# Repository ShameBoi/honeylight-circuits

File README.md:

# Circuit files for Honeylight

KiCad project files for the Honeylight LED board and the Honeylight power/processor board.

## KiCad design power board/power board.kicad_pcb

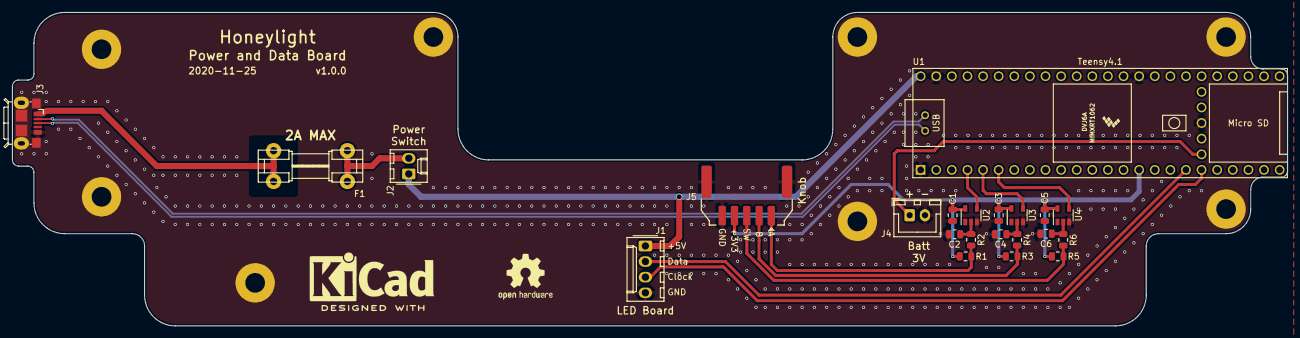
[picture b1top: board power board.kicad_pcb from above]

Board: 2 copper layers, 207.5 x 51.0 mm, 30 parts (0 on the bottom side), 19 nets.

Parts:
C1, C3, C5: 100nF; C_0805_2012Metric
C2, C4, C6: 10nF; C_0805_2012Metric
F1: 2A; Fuseholder5x15_horiz_open_lateral_Type-II
H1: Hole A; MountingHole_3.2mm_M3_Pad
H2: Hole B; MountingHole_3.2mm_M3_Pad
H3: Hole C; MountingHole_3.2mm_M3_Pad
H4: Hole D; MountingHole_3.2mm_M3_Pad
H5: Hole E; MountingHole_3.2mm_M3_Pad
H6: Hole F; MountingHole_3.2mm_M3_Pad
H7: Hole G; MountingHole_3.2mm_M3_Pad
H8: Hole H; MountingHole_3.2mm_M3_Pad
J1: LED Board; Molex_KK-254_AE-6410-04A_1x04_P2.54mm_Vertical
J2: Power Switch; Molex_KK-254_AE-6410-02A_1x02_P2.54mm_Vertical
J3: USB In; USB-Micro-B-FCI-10118193-0001LF
J4: Batt; JST_XH_B2B-XH-A_1x02_P2.50mm_Vertical
J5: Knob; Molex_DuraClik_502352-05XX_1x05-1MP-P2.00mm_SMD_Horizontal
R1, R3, R5: 10K; R_0805_2012Metric
R2, R4, R6: 100; R_0805_2012Metric
U1: Teensy4.1; Teensy41
U2, U3, U4: 74AHC1G14; SOT-23-5

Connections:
+3V3: C1.1, C3.1, C5.1, J5.4, R1.1, R3.1, R5.1, U1.15, U2.5, U3.5, U4.5
+5V: J1.1, J2.1, U1.48
/Clock: J1.3, U1.19
/D+: J3.3, U1.67
/D-: J3.2, U1.66
/Data: J1.2, U1.18
/Debounce Encoder A/Input-Filter: C2.1, R2.1, U2.2
/Debounce Encoder B/Input-Filter: C4.1, R4.1, U3.2
/Debounce Switch/Input-Filter: C6.1, R6.1, U4.2
/Debounced-Encoder-A: U1.4, U2.4
/Debounced-Encoder-B: U1.5, U3.4
/Debounced-Switch: U1.6, U4.4
/Knob-Encoder-A: J5.1, R1.2, R2.2
/Knob-Encoder-B: J5.2, R3.2, R4.2
/Knob-SW: J5.3, R5.2, R6.2
/VBUS-Raw: F1.1, J3.1
/VBatt: J4.1, U1.50
GND: C1.2, C2.2, C3.2, C4.2, C5.2, C6.2, H1.1, H2.1, H3.1, H4.1, H5.1, H6.1, H7.1, H8.1, J1.4, J3.5, J3.6, J4.2, J5.5, J5.MP, U1.1, U1.34, U1.47, U1.52, U2.3, U3.3, U4.3
unnamed: F1.2, J2.2

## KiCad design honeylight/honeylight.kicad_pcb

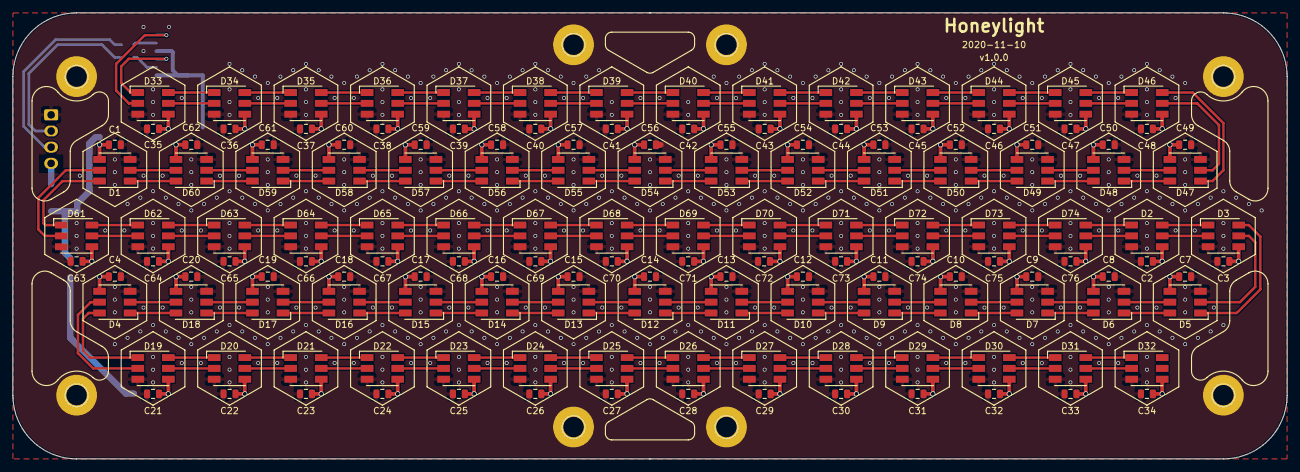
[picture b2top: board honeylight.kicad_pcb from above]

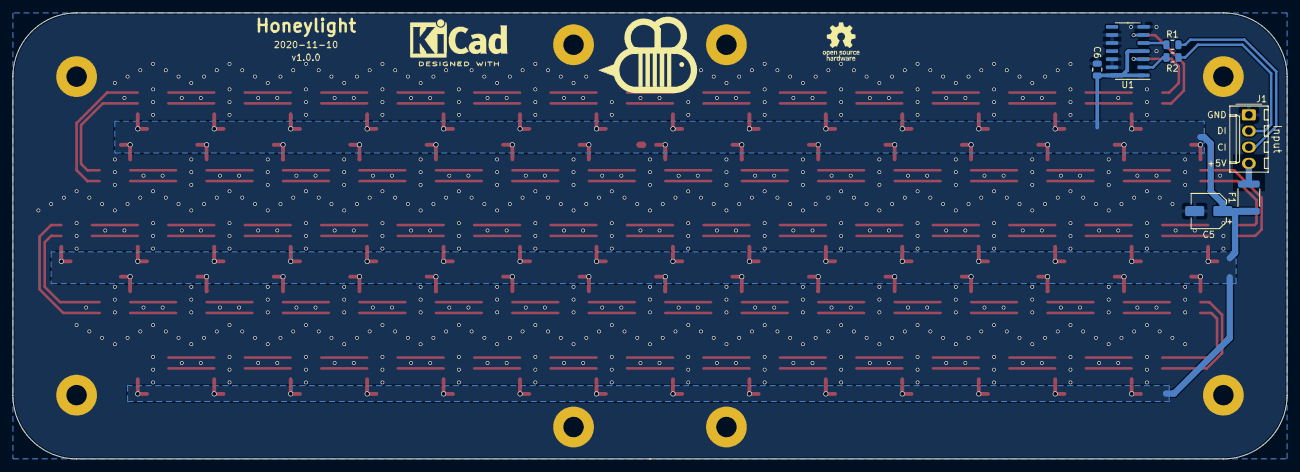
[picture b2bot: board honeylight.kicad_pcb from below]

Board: 2 copper layers, 200.0 x 70.0 mm, 163 parts (7 on the bottom side), 155 nets.

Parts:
C1, C2, C3, C4, C6, C7, C8, C9, C10, C11, C12, C13, C14, C15, C16, C17, C18, C19, C20, C21, C22, C23, C24, C25, C26, C27, C28, C29, C30, C31, C32, C33, C34, C35, C36, C37, C38, C39, C40, C41, C42, C43, C44, C45, C46, C47, C48, C49, C50, C51, C52, C53, C54, C55, C56, C57, C58, C59, C60, C61, C62, C63, C64, C65, C66, C67, C68, C69, C70, C71, C72, C73, C74, C75, C76: 100nF; C_0805_2012Metric
C5: 120uF; CP_Elec_5x5.8
D1, D2, D3, D4, D5, D6, D7, D8, D9, D10, D11, D12, D13, D14, D15, D16, D17, D18, D19, D20, D21, D22, D23, D24, D25, D26, D27, D28, D29, D30, D31, D32, D33, D34, D35, D36, D37, D38, D39, D40, D41, D42, D43, D44, D45, D46, D47, D48, D49, D50, D51, D52, D53, D54, D55, D56, D57, D58, D59, D60, D61, D62, D63, D64, D65, D66, D67, D68, D69, D70, D71, D72, D73, D74: APA102C; LED_RGB_5050-6
F1: 1.25A; Fuse_1812_4532Metric
H1: Hole A; MountingHole_3.2mm_M3_Pad
H2: Hole B; MountingHole_3.2mm_M3_Pad
H3: Hole C; MountingHole_3.2mm_M3_Pad
H4: Hole D; MountingHole_3.2mm_M3_Pad
H5: Hole E; MountingHole_3.2mm_M3_Pad
H6: Hole F; MountingHole_3.2mm_M3_Pad
H7: Hole G; MountingHole_3.2mm_M3_Pad
H8: Hole H; MountingHole_3.2mm_M3_Pad
J1: Input; Molex_KK-254_AE-6410-04A_1x04_P2.54mm_Vertical
R1, R2: 22; R_0805_2012Metric
U1: 74AHCT126; SOIC-14_3.9x8.7mm_P1.27mm

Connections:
+5V: C1.1, C2.1, C3.1, C4.1, C5.1, C6.2, C7.1, C8.1, C9.1, C10.1, C11.1, C12.1, C13.1, C14.1, C15.1, C16.1, C17.1, C18.1, C19.1, C20.1, C21.1, C22.1, C23.1, C24.1, C25.1, C26.1, C27.1, C28.1, C29.1, C30.1, C31.1, C32.1, C33.1, C34.1, C35.1, C36.1, C37.1, C38.1, C39.1, C40.1, C41.1, C42.1, C43.1, C44.1, C45.1, C46.1, C47.1, C48.1, C49.1, C50.1, C51.1, C52.1, C53.1, C54.1, C55.1, C56.1, C57.1, C58.1, C59.1, C60.1, C61.1, C62.1, C63.1, C64.1, C65.1, C66.1, C67.1, C68.1, C69.1, C70.1, C71.1, C72.1, C73.1, C74.1, C75.1, C76.1, D1.4, D2.4, D3.4, D4.4, D5.4, D6.4, D7.4, D8.4, D9.4, D10.4, D11.4, D12.4, D13.4, D14.4, D15.4, D16.4, D17.4, D18.4, D19.4, D20.4, D21.4, D22.4, D23.4, D24.4, D25.4, D26.4, D27.4, D28.4, D29.4, D30.4, D31.4, D32.4, D33.4, D34.4, D35.4, D36.4, D37.4, D38.4, D39.4, D40.4, D41.4, D42.4, D43.4, D44.4, D45.4, D46.4, D47.4, D48.4, D49.4, D50.4, D51.4, D52.4, D53.4, D54.4, D55.4, D56.4, D57.4, D58.4, D59.4, D60.4, D61.4, D62.4, D63.4, D64.4, D65.4, D66.4, D67.4, D68.4, D69.4, D70.4, D71.4, D72.4, D73.4, D74.4, F1.1, U1.1, U1.4, U1.14
/+5V-Pre-Fuse: F1.2, J1.4
/CI: D33.2, U1.6
/CI-Limited: R1.1, U1.5
/CI-Raw: J1.3, R1.2
/DI: D33.1, U1.3
/DI-Limited: R2.1, U1.2
/DI-Raw: J1.2, R2.2
/Row 2/CI: D46.5, D47.2
/Row 2/CO: D1.2, D60.5
/Row 2/DI: D46.6, D47.1
/Row 2/DO: D1.1, D60.6
/Row 3/CI: D1.5, D61.2
/Row 3/CO: D2.2, D74.5
/Row 3/DI: D1.6, D61.1
/Row 3/DO: D2.1, D74.6
/Row 4/CI: D3.5, D5.2
/Row 4/CO: D4.2, D18.5
/Row 4/DI: D3.6, D5.1
/Row 4/DO: D4.1, D18.6
/Row 5/CI: D4.5, D19.2
/Row 5/DI: D4.6, D19.1
GND: C1.2, C2.2, C3.2, C4.2, C5.2, C6.1, C7.2, C8.2, C9.2, C10.2, C11.2, C12.2, C13.2, C14.2, C15.2, C16.2, C17.2, C18.2, C19.2, C20.2, C21.2, C22.2, C23.2, C24.2, C25.2, C26.2, C27.2, C28.2, C29.2, C30.2, C31.2, C32.2, C33.2, C34.2, C35.2, C36.2, C37.2, C38.2, C39.2, C40.2, C41.2, C42.2, C43.2, C44.2, C45.2, C46.2, C47.2, C48.2, C49.2, C50.2, C51.2, C52.2, C53.2, C54.2, C55.2, C56.2, C57.2, C58.2, C59.2, C60.2, C61.2, C62.2, C63.2, C64.2, C65.2, C66.2, C67.2, C68.2, C69.2, C70.2, C71.2, C72.2, C73.2, C74.2, C75.2, C76.2, D1.3, D2.3, D3.3, D4.3, D5.3, D6.3, D7.3, D8.3, D9.3, D10.3, D11.3, D12.3, D13.3, D14.3, D15.3, D16.3, D17.3, D18.3, D19.3, D20.3, D21.3, D22.3, D23.3, D24.3, D25.3, D26.3, D27.3, D28.3, D29.3, D30.3, D31.3, D32.3, D33.3, D34.3, D35.3, D36.3, D37.3, D38.3, D39.3, D40.3, D41.3, D42.3, D43.3, D44.3, D45.3, D46.3, D47.3, D48.3, D49.3, D50.3, D51.3, D52.3, D53.3, D54.3, D55.3, D56.3, D57.3, D58.3, D59.3, D60.3, D61.3, D62.3, D63.3, D64.3, D65.3, D66.3, D67.3, D68.3, D69.3, D70.3, D71.3, D72.3, D73.3, D74.3, H1.1, H2.1, H3.1, H4.1, H5.1, H6.1, H7.1, H8.1, J1.1, U1.7, U1.9, U1.10, U1.12, U1.13
unnamed: D2.5, D3.2
unnamed: D2.6, D3.1
unnamed: D5.5, D6.2
unnamed: D5.6, D6.1
unnamed: D6.5, D7.2
unnamed: D6.6, D7.1
unnamed: D7.5, D8.2
unnamed: D7.6, D8.1
unnamed: D8.5, D9.2
unnamed: D8.6, D9.1
unnamed: D9.6, D10.1
unnamed: D9.5, D10.2
unnamed: D10.5, D11.2
unnamed: D10.6, D11.1
unnamed: D11.5, D12.2
unnamed: D11.6, D12.1
unnamed: D12.5, D13.2
unnamed: D12.6, D13.1
unnamed: D13.5, D14.2
unnamed: D13.6, D14.1
unnamed: D14.5, D15.2
unnamed: D14.6, D15.1
unnamed: D15.5, D16.2
unnamed: D15.6, D16.1
unnamed: D16.5, D17.2
unnamed: D16.6, D17.1
unnamed: D17.5, D18.2
unnamed: D17.6, D18.1
unnamed: D19.5, D20.2
unnamed: D19.6, D20.1
unnamed: D20.5, D21.2
unnamed: D20.6, D21.1
unnamed: D21.5, D22.2
unnamed: D21.6, D22.1
unnamed: D22.5, D23.2
unnamed: D22.6, D23.1
unnamed: D23.5, D24.2
unnamed: D23.6, D24.1
unnamed: D24.5, D25.2
unnamed: D24.6, D25.1
unnamed: D25.5, D26.2
unnamed: D25.6, D26.1
unnamed: D26.5, D27.2
unnamed: D26.6, D27.1
unnamed: D27.5, D28.2
unnamed: D27.6, D28.1
unnamed: D28.5, D29.2
unnamed: D28.6, D29.1
unnamed: D29.5, D30.2
unnamed: D29.6, D30.1
unnamed: D30.5, D31.2
unnamed: D30.6, D31.1
unnamed: D31.5, D32.2
unnamed: D31.6, D32.1
unnamed: D33.5, D34.2
unnamed: D33.6, D34.1
unnamed: D34.5, D35.2
unnamed: D34.6, D35.1
unnamed: D35.5, D36.2
unnamed: D35.6, D36.1
unnamed: D36.5, D37.2
unnamed: D36.6, D37.1
unnamed: D37.5, D38.2
unnamed: D37.6, D38.1
unnamed: D38.5, D39.2
unnamed: D38.6, D39.1
unnamed: D39.5, D40.2
unnamed: D39.6, D40.1
unnamed: D40.5, D41.2
unnamed: D40.6, D41.1
unnamed: D41.5, D42.2
unnamed: D41.6, D42.1
unnamed: D42.5, D43.2
unnamed: D42.6, D43.1
unnamed: D43.5, D44.2
unnamed: D43.6, D44.1
unnamed: D44.5, D45.2
unnamed: D44.6, D45.1
unnamed: D45.5, D46.2
unnamed: D45.6, D46.1
unnamed: D47.5, D48.2
unnamed: D47.6, D48.1
unnamed: D48.5, D49.2
unnamed: D48.6, D49.1
unnamed: D49.5, D50.2
unnamed: D49.6, D50.1
unnamed: D50.5, D51.2
unnamed: D50.6, D51.1
unnamed: D51.5, D52.2
unnamed: D51.6, D52.1
unnamed: D52.5, D53.2
unnamed: D52.6, D53.1
unnamed: D53.5, D54.2
unnamed: D53.6, D54.1
unnamed: D54.5, D55.2
unnamed: D54.6, D55.1
unnamed: D55.5, D56.2
unnamed: D55.6, D56.1
unnamed: D56.5, D57.2
unnamed: D56.6, D57.1
unnamed: D57.5, D58.2
unnamed: D57.6, D58.1
unnamed: D58.5, D59.2
unnamed: D58.6, D59.1
unnamed: D59.5, D60.2
unnamed: D59.6, D60.1
unnamed: D61.5, D62.2
unnamed: D61.6, D62.1
unnamed: D62.5, D63.2
unnamed: D62.6, D63.1
unnamed: D63.5, D64.2
unnamed: D63.6, D64.1
unnamed: D64.5, D65.2
unnamed: D64.6, D65.1
unnamed: D65.5, D66.2
unnamed: D65.6, D66.1
unnamed: D66.5, D67.2
unnamed: D66.6, D67.1
unnamed: D67.5, D68.2
unnamed: D67.6, D68.1
unnamed: D68.5, D69.2
unnamed: D68.6, D69.1
unnamed: D69.5, D70.2
unnamed: D69.6, D70.1
unnamed: D70.5, D71.2
unnamed: D70.6, D71.1
unnamed: D71.5, D72.2
unnamed: D71.6, D72.1
unnamed: D72.5, D73.2
unnamed: D72.6, D73.1
unnamed: D73.5, D74.2
unnamed: D73.6, D74.1

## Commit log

2020-12-20 Initial Commit / v1.0.0 Gerbers
2020-12-20 Forgot 3D directory gitignore
